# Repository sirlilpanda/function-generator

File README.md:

# function-generator
[WARNING] THIS BOARD HAS NOT BEEN BUILT YET AND MAY NOT WORK

Simple stm32G4 based function generator.

has USART, and I2S, with 4 DAC outputs. DACs can be controlled with switches on the board to select their waveforms frequency and phase.

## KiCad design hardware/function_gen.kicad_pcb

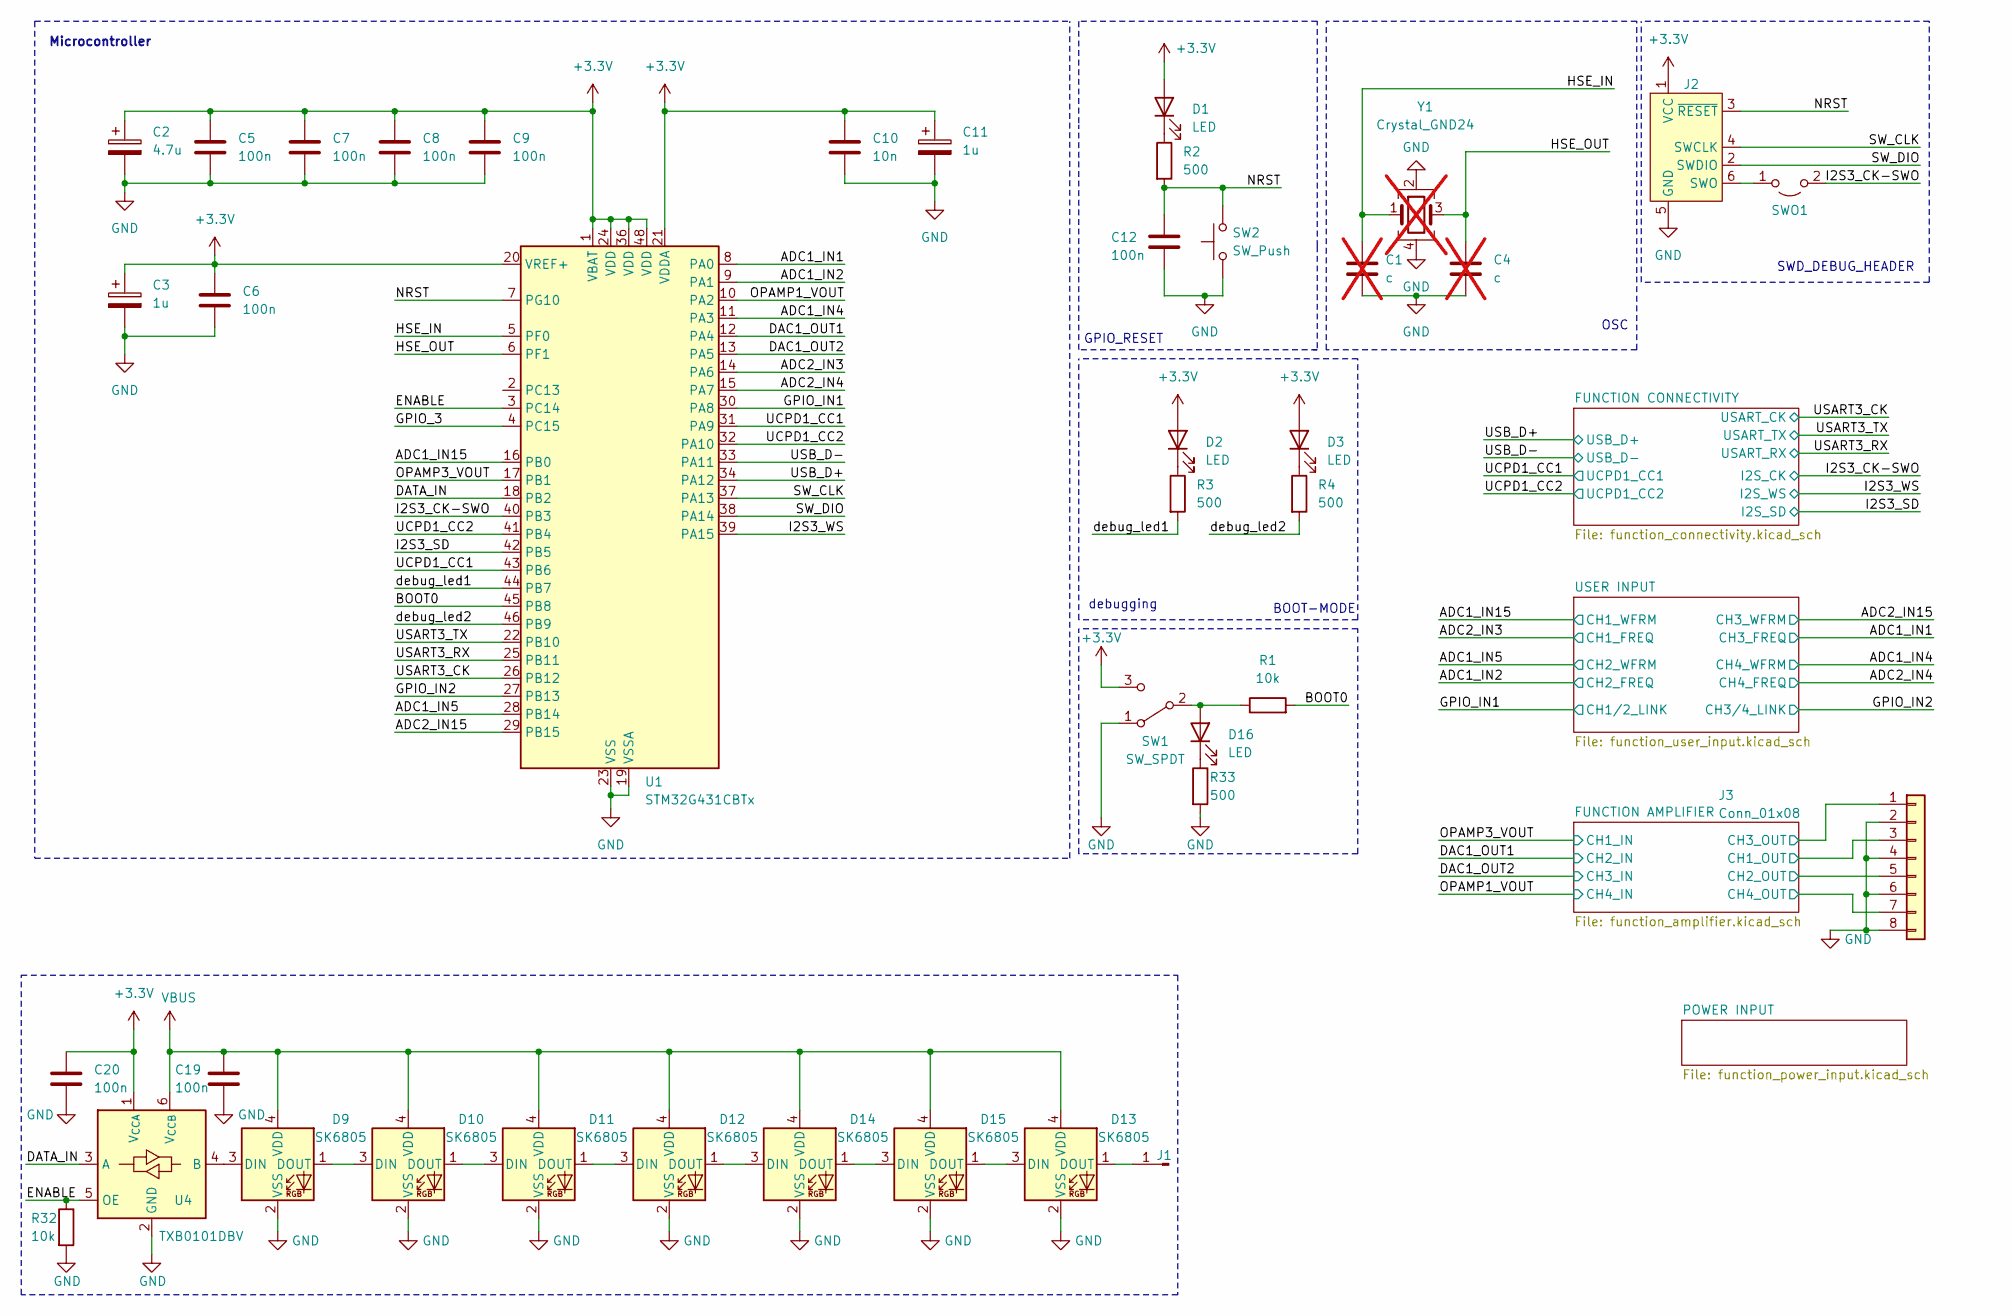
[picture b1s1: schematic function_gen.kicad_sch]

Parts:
C1, C4: c; C_0805_2012Metric; not fitted
C2: 4.7u; C_0805_2012Metric
C3, C11: 1u; C_0805_2012Metric
C5, C6, C7, C8, C9, C12, C19, C20: 100n; C_0805_2012Metric
C10: 10n; C_0805_2012Metric
D1, D2, D3, D16: LED; LED_0805_2012Metric
D9, D10, D11, D12, D13, D14, D15: SK6805; LED_SK6805_PLCC4_2.4x2.7mm_P1.3mm
J1: Conn_01x01_Pin; TestPoint_Pad_1.5x1.5mm
J2: Conn_ARM_SWD_TagConnect_TC2030-NL; Tag-Connect_TC2030-IDC-NL_2x03_P1.27mm_Vertical
J3: Conn_01x08; PinHeader_1x08_P2.54mm_Horizontal
R1, R32: 10k; R_0805_2012Metric
R2, R3, R4, R33: 500; R_0805_2012Metric
SW1: SW_SPDT; SW_Slide_SPDT_Angled_CK_OS102011MA1Q
SW2: SW_Push; SW_Push_SPST_NO_Alps_SKRK
SWO1: Jumper_2_Open; SolderJumper-2_P1.3mm_Open_Pad1.0x1.5mm
U1: STM32G431CBTx; LQFP-48_7x7mm_P0.5mm
U4: TXB0101DBV; SOT-23-6
Y1: Crystal_GND24; Crystal_SMD_SeikoEpson_FA238V-4Pin_3.2x2.5mm_HandSoldering; not fitted

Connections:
/ADC1_IN1: U1.8 (PA0); also elsewhere on the board
/ADC1_IN2: U1.9 (PA1); also elsewhere on the board
/ADC1_IN4: U1.11 (PA3); also elsewhere on the board
/ADC1_IN5: U1.28 (PB14); also elsewhere on the board
/ADC1_IN15: U1.16 (PB0); also elsewhere on the board
/ADC2_IN3: U1.14 (PA6); also elsewhere on the board
/ADC2_IN4: U1.15 (PA7); also elsewhere on the board
/ADC2_IN15: U1.29 (PB15); also elsewhere on the board
/BOOT0: R1.2, U1.45 (PB8)
/DAC1_OUT1: U1.12 (PA4); also elsewhere on the board
/DATA_IN: U1.18 (PB2), U4.3 (A)
/ENABLE: R32.1, U1.3 (PC14), U4.5 (OE)
/FUNCTION AMPLIFIER/CH1_OUT: J3.3; also elsewhere on the board
/FUNCTION AMPLIFIER/CH2_OUT: J3.5; also elsewhere on the board
/FUNCTION AMPLIFIER/CH3_OUT: J3.1; also elsewhere on the board
/FUNCTION AMPLIFIER/CH4_OUT: J3.7; also elsewhere on the board
/GPIO_3: U1.4 (PC15)
/GPIO_IN1: U1.30 (PA8); also elsewhere on the board
/GPIO_IN2: U1.27 (PB13); also elsewhere on the board
/HSE_IN: C1.1, U1.5 (PF0), Y1.1
/HSE_OUT: C4.1, U1.6 (PF1), Y1.3
/I2S3_CK-SWO: SWO1.2 (B), U1.40 (PB3); also elsewhere on the board
/I2S3_SD: U1.42 (PB5); also elsewhere on the board
/I2S3_WS: U1.39 (PA15); also elsewhere on the board
/NRST: C12.2, J2.3 (~RESET), R2.2, SW2.2, U1.7 (PG10)
/OPAMP1_VOUT: U1.10 (PA2); also elsewhere on the board
/SW_CLK: J2.4 (SWCLK), U1.37 (PA13)
/SW_DIO: J2.2 (SWDIO), U1.38 (PA14)
/UCPD1_CC1: U1.31 (PA9), U1.43 (PB6); also elsewhere on the board
/UCPD1_CC2: U1.32 (PA10), U1.41 (PB4); also elsewhere on the board
/USART3_CK: U1.26 (PB12); also elsewhere on the board
/USART3_RX: U1.25 (PB11); also elsewhere on the board
/USART3_TX: U1.22 (PB10); also elsewhere on the board
/USB_D+: U1.34 (PA12); also elsewhere on the board
/USB_D-: U1.33 (PA11); also elsewhere on the board
/debug_led1: R3.2, U1.44 (PB7)
/debug_led2: R4.2, U1.46 (PB9)
GND: C1.2, C2.2, C3.2, C4.2, C5.2, C6.2, C7.2, C8.2, C9.2, C10.2, C11.2, C12.1, C19.2, C20.2, D9.2 (VSS), D10.2 (VSS), D11.2 (VSS), D12.2 (VSS), D13.2 (VSS), D14.2 (VSS), D15.2 (VSS), J2.5 (GND), J3.2, J3.4, J3.6, J3.8, R32.2, R33.2, SW1.1 (A), SW2.1, U1.19 (VSSA), U1.23 (VSS), U1.35 (VSS), U1.47 (VSS), U4.2 (GND), Y1.2, Y1.4; also elsewhere on the board
unnamed: D1.1 (K), R2.1
unnamed: D2.1 (K), R3.1
unnamed: D3.1 (K), R4.1
unnamed: D9.3 (DIN), U4.4 (B)
unnamed: D9.1 (DOUT), D10.3 (DIN)
unnamed: D10.1 (DOUT), D11.3 (DIN)
unnamed: D11.1 (DOUT), D12.3 (DIN)
unnamed: D12.1 (DOUT), D14.3 (DIN)
unnamed: D13.3 (DIN), D15.1 (DOUT)
unnamed: D13.1 (DOUT), J1.1
unnamed: D14.1 (DOUT), D15.3 (DIN)
unnamed: D16.2 (A), R1.1, SW1.2 (B)
unnamed: D16.1 (K), R33.1
unnamed: J2.6 (SWO), SWO1.1 (A)

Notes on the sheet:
SWD_DEBUG_HEADER
Microcontroller
debugging
BOOT-MODE
GPIO_RESET
OSC

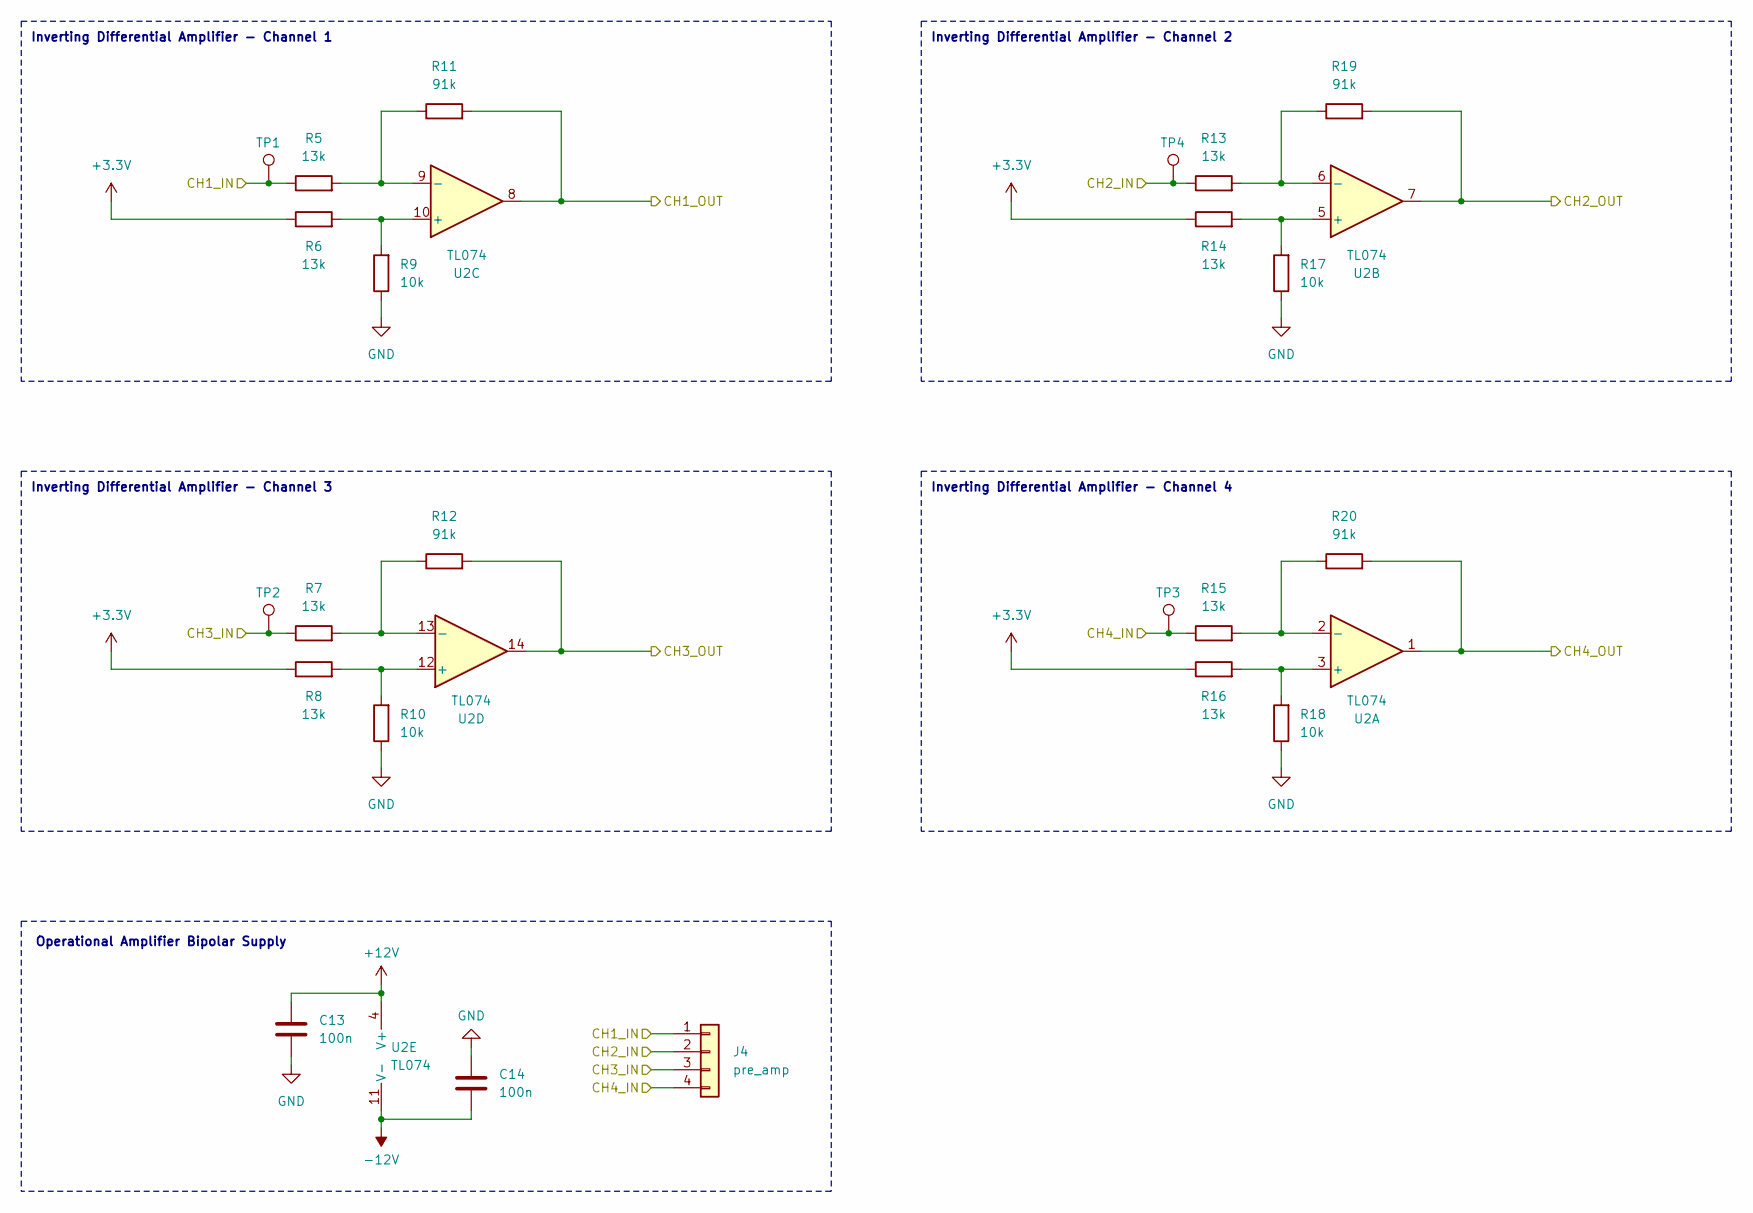
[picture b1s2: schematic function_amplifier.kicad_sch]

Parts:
C13, C14: 100n; C_0805_2012Metric
J4: pre_amp
R5, R6, R7, R8, R13, R14, R15, R16: 13k; R_0805_2012Metric
R9, R10, R17, R18: 10k; R_0805_2012Metric
R11, R12, R19, R20: 91k; R_0805_2012Metric
TP1, TP2, TP3, TP4: TestPoint; TestPoint_Pad_D1.5mm
U2: TL074; SOIC-14_3.9x8.7mm_P1.27mm

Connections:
+12V: C13.1, U2.4 (V+); also elsewhere on the board
-12V: C14.2, U2.11 (V-); also elsewhere on the board
/DAC1_OUT1: R13.1; also elsewhere on the board
/FUNCTION AMPLIFIER/CH1_OUT: R11.2, U2.8; also elsewhere on the board
/FUNCTION AMPLIFIER/CH2_OUT: R19.2, U2.7; also elsewhere on the board
/FUNCTION AMPLIFIER/CH3_OUT: R12.2, U2.14; also elsewhere on the board
/FUNCTION AMPLIFIER/CH4_OUT: R20.2, U2.1; also elsewhere on the board
/OPAMP1_VOUT: R15.1; also elsewhere on the board
GND: C13.2, C14.1, R9.1, R10.1, R17.1, R18.1; also elsewhere on the board
unnamed: R16.2, R18.2, U2.3 (+)
unnamed: R15.2, R20.1, U2.2 (-)
unnamed: R14.2, R17.2, U2.5 (+)
unnamed: R13.2, R19.1, U2.6 (-)
unnamed: R6.2, R9.2, U2.10 (+)
unnamed: R5.2, R11.1, U2.9 (-)
unnamed: R8.2, R10.2, U2.12 (+)
unnamed: R7.2, R12.1, U2.13 (-)

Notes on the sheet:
Inverting Differential Amplifier - Channel 4
Inverting Differential Amplifier - Channel 2
Operational Amplifier Bipolar Supply
Inverting Differential Amplifier - Channel 3
Inverting Differential Amplifier - Channel 1

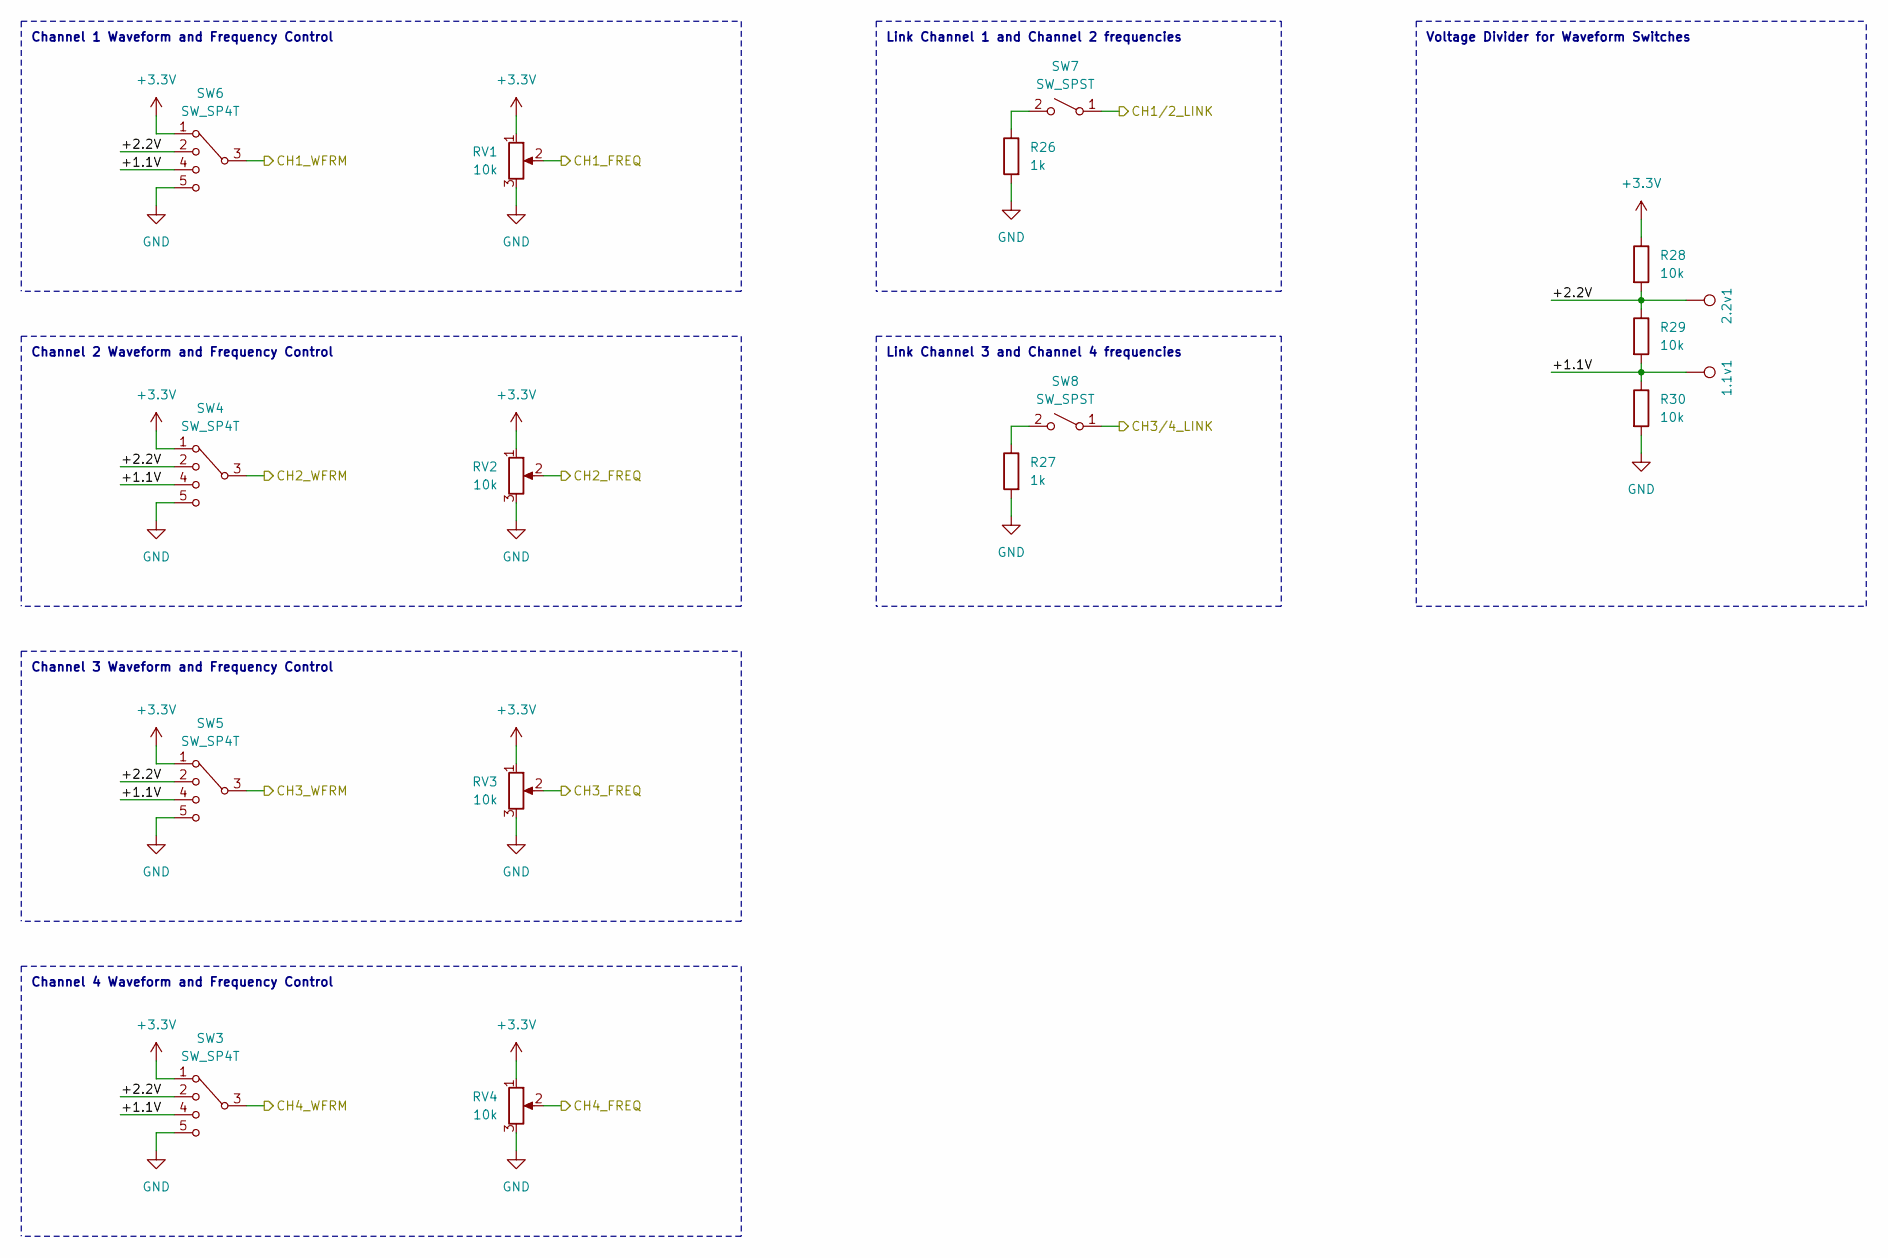
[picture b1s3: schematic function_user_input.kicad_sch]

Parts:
1.1v1, 2.2v1: TestPoint; TestPoint_Pad_D1.5mm
R26, R27: 1k; R_0805_2012Metric
R28, R29, R30: 10k; R_0805_2012Metric
RV1, RV2, RV3, RV4: 10k; Potentiometer_Vishay_T73YP_Vertical
SW3, SW4, SW5, SW6: SW_SP4T; SLB1470
SW7, SW8: SW_SPST; SW_E-Switch_EG1271_SPDT

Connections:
/ADC1_IN1: RV3.2; also elsewhere on the board
/ADC1_IN2: RV2.2; also elsewhere on the board
/ADC1_IN4: SW3.3; also elsewhere on the board
/ADC1_IN5: SW4.3; also elsewhere on the board
/ADC1_IN15: SW6.3; also elsewhere on the board
/ADC2_IN3: RV1.2; also elsewhere on the board
/ADC2_IN4: RV4.2; also elsewhere on the board
/ADC2_IN15: SW5.3; also elsewhere on the board
/GPIO_IN1: SW7.1 (A); also elsewhere on the board
/GPIO_IN2: SW8.1 (A); also elsewhere on the board
/USER INPUT/+1.1V: 1.1v1.1, R29.2, R30.1, SW3.4, SW4.4, SW5.4, SW6.4
/USER INPUT/+2.2V: 2.2v1.1, R28.2, R29.1, SW3.2, SW4.2, SW5.2, SW6.2
GND: R26.2, R27.2, R30.2, RV1.3, RV2.3, RV3.3, RV4.3, SW3.5, SW4.5, SW5.5, SW6.5; also elsewhere on the board
unnamed: R26.1, SW7.2 (B)
unnamed: R27.1, SW8.2 (B)

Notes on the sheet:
Channel 4 Waveform and Frequency Control
Channel 2 Waveform and Frequency Control
Link Channel 1 and Channel 2 frequencies
Link Channel 3 and Channel 4 frequencies
Channel 1 Waveform and Frequency Control
Channel 3 Waveform and Frequency Control
Voltage Divider for Waveform Switches

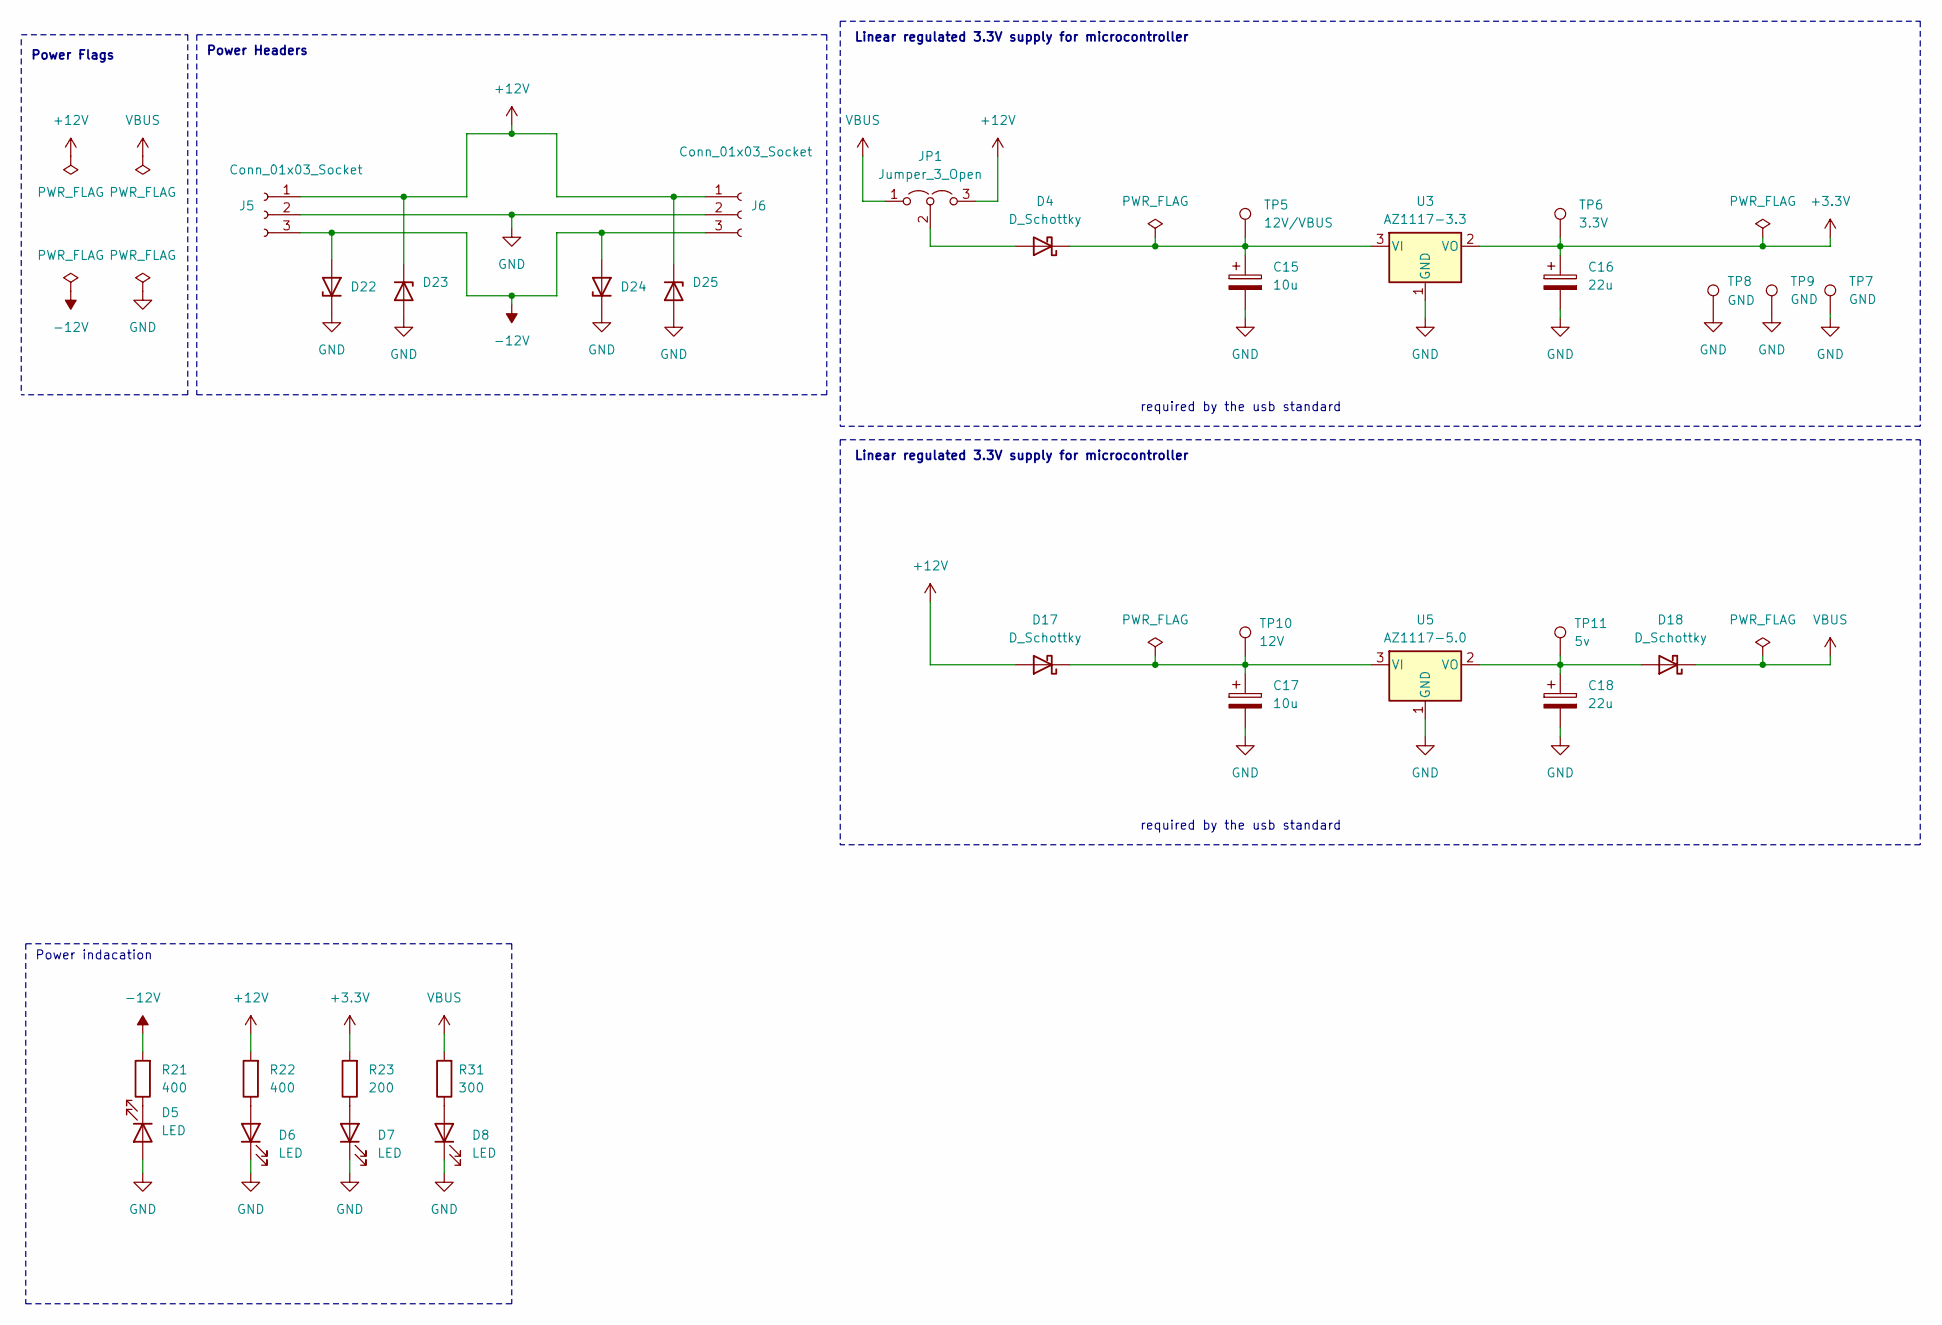
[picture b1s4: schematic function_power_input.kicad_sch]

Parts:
C15, C17: 10u; C_0805_2012Metric
C16, C18: 22u; C_0805_2012Metric
D4, D17, D18: D_Schottky; D_0805_2012Metric
D5, D6, D7, D8: LED; LED_0805_2012Metric
D22, D23, D24, D25: PTVS12VZ1USK; Nexperia_DSN1608-2_1.6x0.8mm
J5: Conn_01x03_Socket; PinHeader_1x03_P2.54mm_Horizontal
J6: Conn_01x03_Socket; PinSocket_1x03_P2.54mm_Vertical
JP1: Jumper_3_Open; SolderJumper-3_P1.3mm_Bridged2Bar12_RoundedPad1.0x1.5mm_Num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
R21, R22: 400; R_0805_2012Metric
R23: 200; R_0805_2012Metric
R31: 300; R_0805_2012Metric
TP5: 12V/VBUS; TestPoint_Pad_D1.5mm
TP6: 3.3V; TestPoint_Pad_D1.5mm
TP7: GND; TestPoint_Pad_D1.5mm
TP8, TP9: GND; TestPoint_Bridge_Pitch2.54mm_Drill0.7mm
TP10: 12V; TestPoint_Pad_D1.5mm
TP11: 5v; TestPoint_Pad_D1.5mm
U3: AZ1117-3.3; SOT-223
U5: AZ1117-5.0; SOT-223

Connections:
+12V: D17.2 (A), D23.1 (K), D25.1 (K), J5.1, J6.1, JP1.3 (B), R22.2; also elsewhere on the board
-12V: D22.2 (A), D24.2 (A), J5.3, J6.3, R21.2; also elsewhere on the board
GND: C15.2, C16.2, C17.2, C18.2, D5.2 (A), D6.1 (K), D7.1 (K), D8.1 (K), D22.1 (K), D23.2 (A), D24.1 (K), D25.2 (A), J5.2, J6.2, TP8.1, TP9.1, U3.1 (GND), U5.1 (GND); also elsewhere on the board
unnamed: D4.2 (A), JP1.2 (C)
unnamed: D5.1 (K), R21.1
unnamed: D6.2 (A), R22.1
unnamed: D7.2 (A), R23.1
unnamed: D8.2 (A), R31.1
unnamed: C17.1, D17.1 (K), TP10.1, U5.3 (VI)
unnamed: C18.1, D18.2 (A), TP11.1, U5.2 (VO)

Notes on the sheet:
Power Headers
Linear regulated 3.3V supply for microcontroller
required by the usb standard
Power Flags
Power indacation

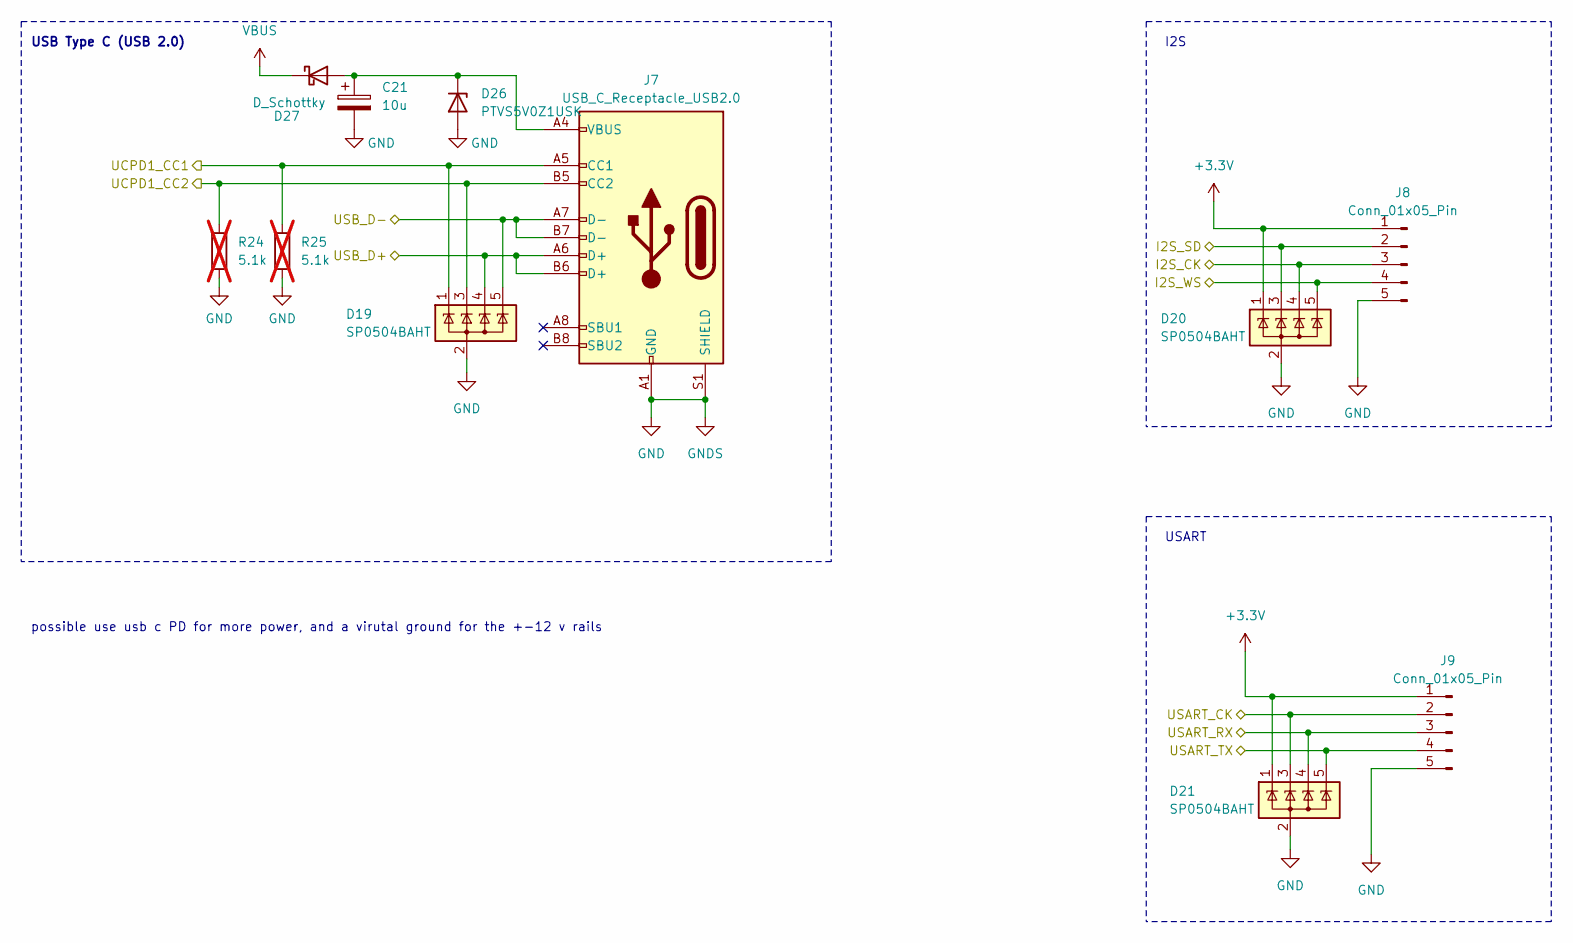
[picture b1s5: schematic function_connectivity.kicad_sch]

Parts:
C21: 10u; C_0805_2012Metric
D19, D20, D21: SP0504BAHT; SOT-23-5
D26: PTVS5V0Z1USK; Nexperia_DSN1608-2_1.6x0.8mm
D27: D_Schottky; D_0805_2012Metric
J7: USB_C_Receptacle_USB2.0; USB_C_Receptacle_HRO_TYPE-C-31-M-12
J8, J9: Conn_01x05_Pin; JST_XH_B5B-XH-AM_1x05_P2.50mm_Vertical
R24, R25: 5.1k; R_0805_2012Metric; not fitted

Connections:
/I2S3_CK-SWO: D20.4 (K), J8.3; also elsewhere on the board
/I2S3_SD: D20.3 (K), J8.2; also elsewhere on the board
/I2S3_WS: D20.5 (K), J8.4; also elsewhere on the board
/UCPD1_CC1: D19.1 (K), J7.A5 (CC1), R25.1; also elsewhere on the board
/UCPD1_CC2: D19.3 (K), J7.B5 (CC2), R24.1; also elsewhere on the board
/USART3_CK: D21.3 (K), J9.2; also elsewhere on the board
/USART3_RX: D21.4 (K), J9.3; also elsewhere on the board
/USART3_TX: D21.5 (K), J9.4; also elsewhere on the board
/USB_D+: D19.4 (K), J7.A6 (D+), J7.B6 (D+); also elsewhere on the board
/USB_D-: D19.5 (K), J7.A7 (D-), J7.B7 (D-); also elsewhere on the board
GND: C21.2, D19.2 (A), D20.2 (A), D21.2 (A), D26.2 (A), J7.A1 (GND), J7.A12 (GND), J7.B1 (GND), J7.B12 (GND), J7.S1 (SHIELD), J8.5, J9.5, R24.2, R25.2; also elsewhere on the board

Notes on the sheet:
USART
I2S
USB Type C (USB 2.0)
possible use usb c PD for more power, and a virutal ground for the +-12 v rails

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
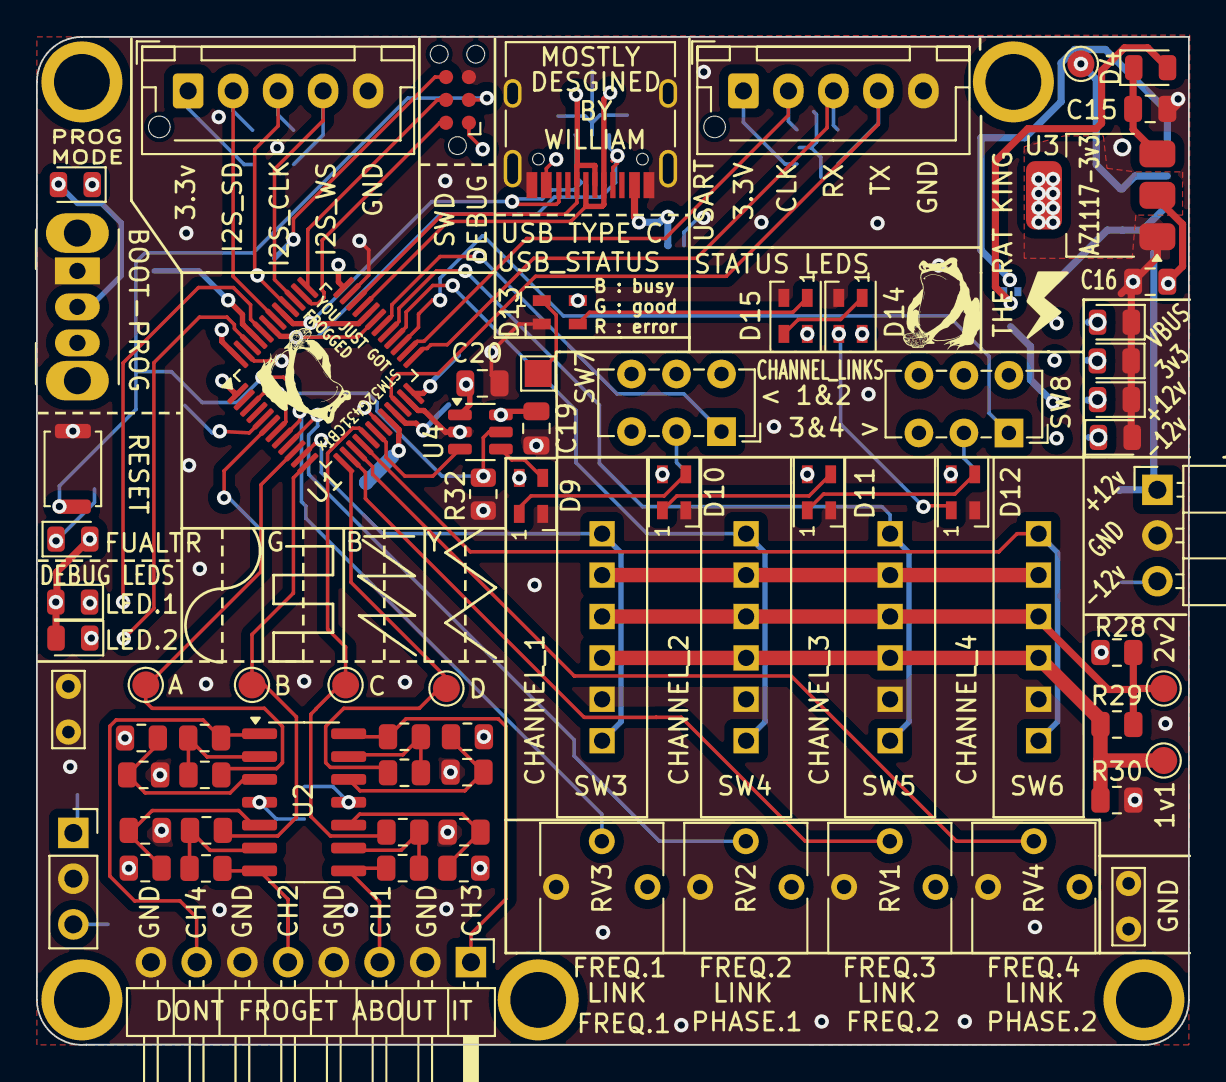
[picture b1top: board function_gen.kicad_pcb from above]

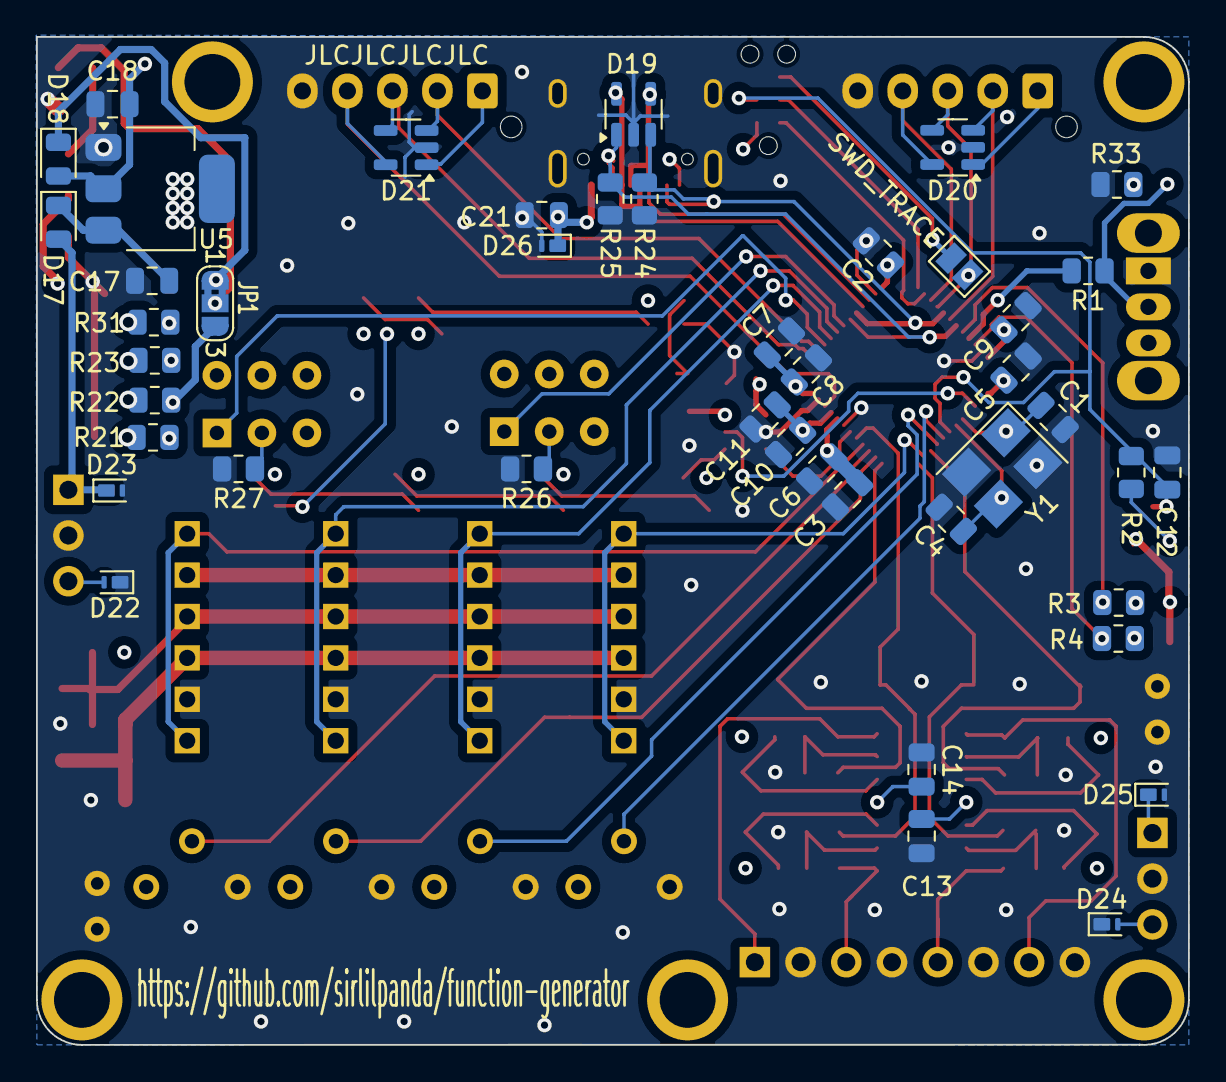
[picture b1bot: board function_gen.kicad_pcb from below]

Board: 4 copper layers, 64.0 x 56.0 mm, 117 parts (44 on the bottom side), 77 nets.

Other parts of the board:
A: TestPoint; TestPoint_Pad_D1.5mm
B: TestPoint; TestPoint_Pad_D1.5mm

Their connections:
/DAC1_OUT1: B.1; also elsewhere on the board
/OPAMP1_VOUT: A.1; also elsewhere on the board

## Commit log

2024-04-04 inital commit
2024-04-04 removed lock file
2024-04-09 auto updated
2024-04-09 added swd header (optional swo), added an led for NRST, added DNP oscillator encase user perfer to use one, added 3 GPIOs
2024-04-09 updated pcb to refelect changes made in the sch
2024-04-09 stm .ioc file that holds the current configuration of the stm32, will hold code later
2024-04-09 updated pdf
2024-04-09 tweaks power traces
2024-04-09 added drawing mesurements for case desgin
2024-04-17 minor changes
2024-05-17 software init
2024-05-18 updated readme for new pcb
2024-05-18 added more ground testpoint for osc prob clip and status led for vbus
2024-05-18 update channel select footprint
2024-05-18 updated to reflect changes made in sch
2024-05-21 adjusted some silk screen
2024-05-21 updated netclass colours
2024-07-24 now works with vscode, lots of auto gened files
2024-07-24 got printf working
2024-09-29 added tvs diodes for eds
2024-09-29 added a 5v reg for when RGB leds need powered from 12v
2024-09-29 updated a footprint
2024-09-29 added RGB LEDs
2024-09-29 complete redesgin
2024-09-29 auto update
2024-09-29 new image
2024-09-29 removed old image
2024-09-29 new pin layout
2024-09-29 changed to new image
2025-03-09 added workflow
2025-03-09 removed setup since it wasnt needed
2025-03-09 now runs on all branches
2025-03-09 added missing dir
